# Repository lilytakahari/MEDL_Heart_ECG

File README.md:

# Electrocardiogram

Accompanying presentation: https://tinyurl.com/ecg-medl-heart

Thank you teammates Daniel Hosseinian, Eric Tang, and Megan Tan; it was ridiculously fun working with y'all!

Autodesk EAGLE files: 

`pcb_design.brd`: PCB schematic

`circuit_design.sch`: ECG circuit schematic

Processing files:

`ECG_display.pde`: ECG signal plotter. Collects 40 seconds of data and saves it to csv

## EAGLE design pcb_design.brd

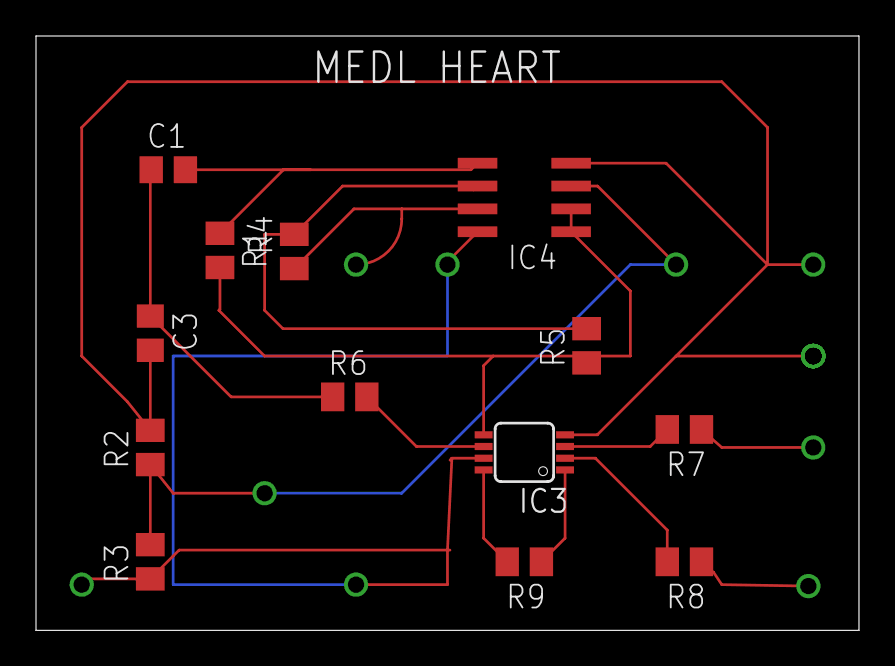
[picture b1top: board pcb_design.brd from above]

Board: 2 copper layers, 45.7 x 33.0 mm, 13 parts (0 on the bottom side), 13 nets.

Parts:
C1, C3: C0805
IC3: AD623RM; MSOP08
IC4: LM4558D; SO08
R1, R4, R5, R6, R7, R8, R9: M0805
R2, R3: 100; M0805

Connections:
0: C3.2, IC3.4, IC4.4, R2.2
+5V: IC3.7, IC4.8, R3.1
unnamed: IC4.3, R2.1, R3.2
unnamed: IC4.6, R4.2, R5.2
unnamed: IC3.5, IC4.1, IC4.2, R1.2, R5.1
unnamed: IC4.7, R4.1
unnamed: C1.2, IC4.5, R1.1
unnamed: C1.1, C3.1, R6.1
unnamed: IC3.6, R6.2
unnamed: IC3.3, R7.2
unnamed: IC3.2, R8.2
unnamed: IC3.1, R9.1
unnamed: IC3.8, R9.2
